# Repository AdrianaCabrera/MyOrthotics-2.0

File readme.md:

# MyOrthotics 2.0 Workshop

MyOrthotics 2.0 is a new version of the Fab Academy final project (MyOrthotics), developed by Adriana Cabrera in 2016 for cases of semi paralysis. 

This version is based on cutting and its purpose is to explore rapid construction for orthotics for first aid cases or temporary use.
The first version of this orthotic workshop was realized in the Fab Lab Kamp-Lintfort Hochschule Rhein Waal for the course of Biomechanics and Biomaterial and for the class of Prof. William Megill. 

The changes of the microcontroller board were designed for the workshop Hands on assistive devices (MyOrthotics 2.0) realized in the international Fab Lab Conference in Santiago de Chile. 

In the repository you can find the template of the splint for men and women to introduction of the topic. For optimal fitting, 3D scanning the patient's arm and hand is recommended. 

1. 3D Scanning
   1. Repairing Mesh Remake
   2. 360 Fusion
   3. Exact Flat 
   4. Folding patterns 
1. Cutting
   1. Illustrator, Rhinoceros, preparing the file
   2. Belt test measurements on your body
   3. Cutting phallanges

1. Electronic
   1. Introduction to soldering 
   2. MyOrthotics SKu Board
   3. Voltage regulator
   4. MyOWare Sensor

1. 3D printing on the surface 

1. Assembly 
   1. Motors 
   2. Exoskeleton 
   3. Phalanges 
1. Wiring

Check in detail the documentation of the project in the following PDF
[MyOrthotics 2.0 Workshop manual](https://github.com/AdrianaCabrera/MyOrthotics-2.0/blob/master/MyOrthotics%20Manual.pdf))

And here you can check the required components in the Bill of Material table:

# Materials

* 0.8 mm x 30mm x30mm Polypropylen-Folie
* 10 Nylon Screws M3 
* 10 Nylon nuts M3
* 3 Servo Motors Torque (no less that 1,5 gr. And 1:60 mm/ s)
* MyoWare Muscle Sensor
* 1 Microcontroller Board MyOrthotics Sku (based on satshakit micro [https://github.com/satshas/satshakit/tree/master/docs/satshakit_micro]())
* Jumper wires
* 1 Battery 3.7 V 750mah 1S 3
* 1 Pololu 5V Step-Up 
* 15 cm Plexiglas or MDF

[Bill of Material](https://docs.google.com/spreadsheets/d/199VWikn73-JOAMEcc2uPSlAMuQEjKREj8A_Vey5oZjk/edit?usp=sharing))

## Authors

* **Adriana Cabrera**
* Contact

* [adriana.cabrera.g@gmail.com]()
* [adriana.cabrera@hochschule-rhein-waal.de]()
* [linkedin](https://www.linkedin.com/in/adrianacabrerag/) 

## Thanks
* [3D-Kompetenzzentrum Niederrhein](https://www.3dzentrum-niederrhein.de/)
* [Fablab Kamp-Lintfort]()
* [Hochschule Rhein-Waal]()
* Friedrich-Heinrich-Allee 25, 47475 Kamp-Lintfort, Germany
* fablab@hochschule-rhein-waal.de 

## License

This work is licensed under the terms of Attribution-NonCommercial-ShareAlike 4.0 International (CC BY-NC-SA 4.0).
Source code is licensed under the terms of the GNU Lesser General Public License v2.1 (LGPL). Adriana Cabrera 2016

## Disclaimer

This hardware/software is provided "as is", and you use the hardware/software at your own risk. Under no circumstances shall any author be liable for direct, indirect, special, incidental, or consequential damages resulting from the use, misuse, or inability to use this hardware/software.

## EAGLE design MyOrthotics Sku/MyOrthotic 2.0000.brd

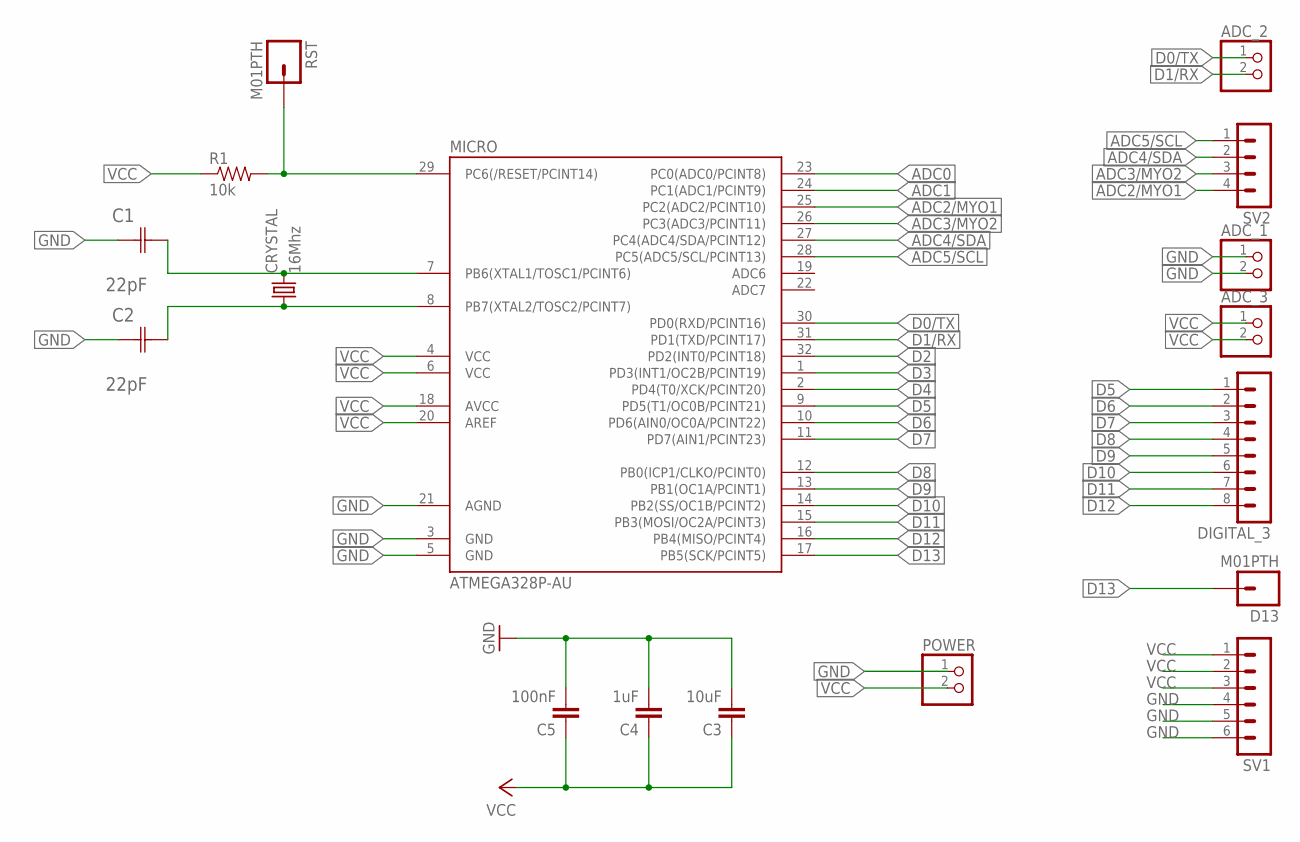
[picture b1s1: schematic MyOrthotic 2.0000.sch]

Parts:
ADC_1, ADC_2, ADC_3: PINHD-1X2; 1X02
C1, C2: 22pF; CAPC3216X178N
C3: 10uF; 1206
C4: 1uF; 1206
C5: 100nF; 1206
CRYSTAL: 16Mhz; CSM-7X-DU
D13: M01PTH; 1X01
DIGITAL_3: MA08-1
MICRO: ATMEGA328P-AU; TQFP32-08
POWER: PINHD-1X2; 1X02
R1: 10k; 1206
RST: M01PTH; 1X01
SV1: MA06-1
SV2: MA04-1

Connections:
ADC0: MICRO.23 (PC0(ADC0/PCINT8))
ADC1: MICRO.24 (PC1(ADC1/PCINT9))
ADC2/MYO1: MICRO.25 (PC2(ADC2/PCINT10)), SV2.4
ADC3/MYO2: MICRO.26 (PC3(ADC3/PCINT11)), SV2.3
ADC4/SDA: MICRO.27 (PC4(ADC4/SDA/PCINT12)), SV2.2
ADC5/SCL: MICRO.28 (PC5(ADC5/SCL/PCINT13)), SV2.1
D0/TX: ADC_2.1, MICRO.30 (PD0(RXD/PCINT16))
D1/RX: ADC_2.2, MICRO.31 (PD1(TXD/PCINT17))
D2: MICRO.32 (PD2(INT0/PCINT18))
D3: MICRO.1 (PD3(INT1/OC2B/PCINT19))
D4: MICRO.2 (PD4(T0/XCK/PCINT20))
D5: DIGITAL_3.1, MICRO.9 (PD5(T1/OC0B/PCINT21))
D6: DIGITAL_3.2, MICRO.10 (PD6(AIN0/OC0A/PCINT22))
D7: DIGITAL_3.3, MICRO.11 (PD7(AIN1/PCINT23))
D8: DIGITAL_3.4, MICRO.12 (PB0(ICP1/CLKO/PCINT0))
D9: DIGITAL_3.5, MICRO.13 (PB1(OC1A/PCINT1))
D10: DIGITAL_3.6, MICRO.14 (PB2(SS/OC1B/PCINT2))
D11: DIGITAL_3.7, MICRO.15 (PB3(MOSI/OC2A/PCINT3))
D12: DIGITAL_3.8, MICRO.16 (PB4(MISO/PCINT4))
D13: D13.1, MICRO.17 (PB5(SCK/PCINT5))
GND: ADC_1.1, ADC_1.2, C1.1 (C1), C2.1 (C1), C3.2, C4.2, C5.2, MICRO.3 (GND), MICRO.5 (GND), MICRO.21 (AGND), POWER.1, SV1.4, SV1.5, SV1.6
unnamed: C1.2 (C2), CRYSTAL.2, MICRO.7 (PB6(XTAL1/TOSC1/PCINT6))
unnamed: MICRO.29 (PC6(/RESET/PCINT14)), R1.2, RST.1
unnamed: C2.2 (C2), CRYSTAL.1, MICRO.8 (PB7(XTAL2/TOSC2/PCINT7))
VCC: ADC_3.1, ADC_3.2, C3.1, C4.1, C5.1, MICRO.4 (VCC), MICRO.6 (VCC), MICRO.18 (AVCC), MICRO.20 (AREF), POWER.2, R1.1, SV1.1, SV1.2, SV1.3

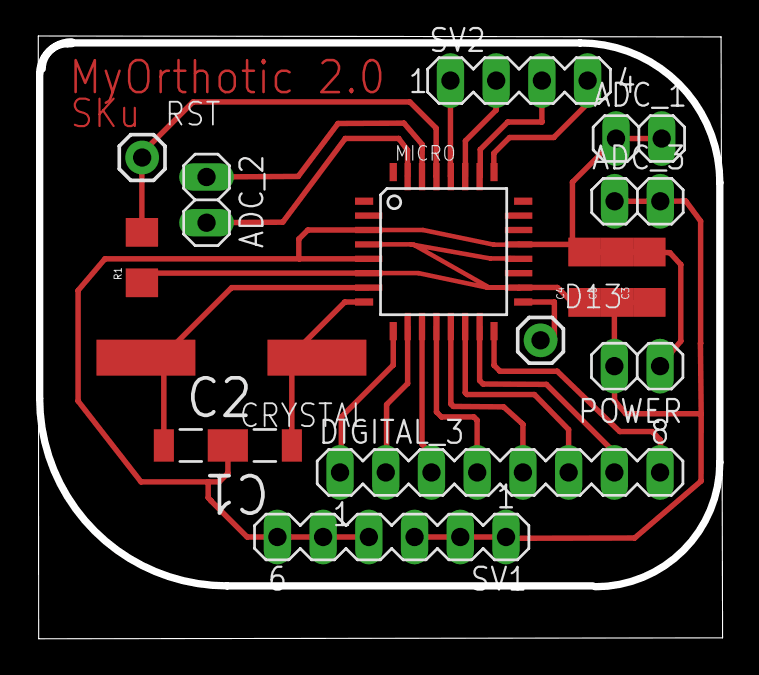
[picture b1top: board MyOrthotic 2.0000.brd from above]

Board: 2 copper layers, 38.0 x 33.5 mm, 17 parts (0 on the bottom side), 20 nets.

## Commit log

2017-10-09 MyOrthotics 2.0
    MyOrthotics 2.0
    Bio inspired structures and human interaction are infinite source of
    inspiration applied in wearables, rehabilitation, prosthetics and other
    assistive devices.The process of making assistive devices has until
    recent years been a long and expensive individualized process,
    requiring detailed development and bespoke labor by physical therapists
2017-10-09 Revert "MyOrthotics 2.0"
    This reverts commit 6eaf257bc11cb9bb3487e516488d6da3ccf82e82.
2017-11-03 Master readme
    Master readme first description
2017-11-08 new repository
    new repository
2017-11-08 change

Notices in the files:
parts and their libraries:
01_SparkFun: Licensing: CC v3.0 Share-Alike You are welcome to use this library for commercial purposes.
